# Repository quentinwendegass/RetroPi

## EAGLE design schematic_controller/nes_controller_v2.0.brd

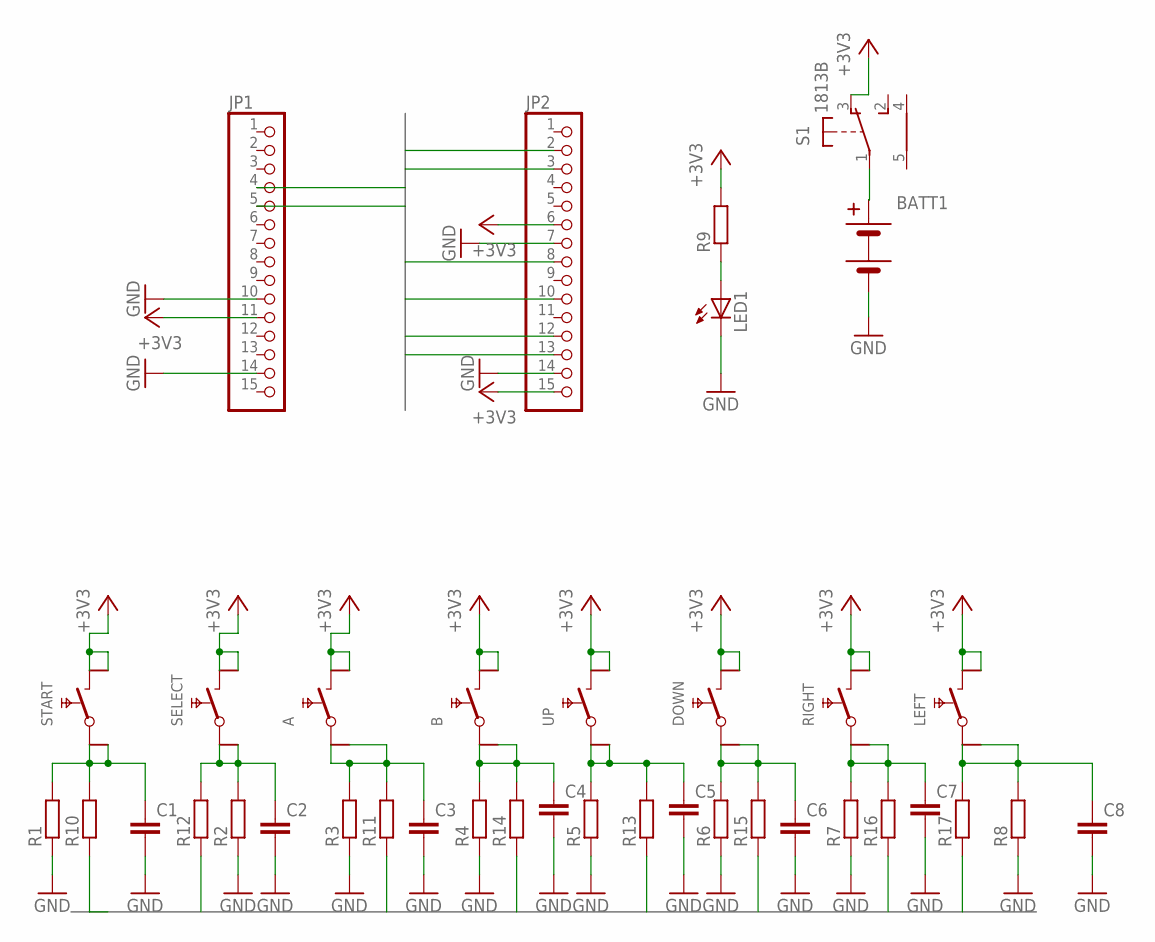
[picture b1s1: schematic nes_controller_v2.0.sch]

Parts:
A: SMDTAST
B: SMDTAST
BATT1: BATTERIEHALTER_2X_AAA; BATTERIEHALTER
C1, C2, C3, C4, C5, C6, C7, C8: C-EUC0805K; C0805K
DOWN: SMDTAST
JP1, JP2: PINHD-1X15; 1X15
LED1: LED3MM
LEFT: SMDTAST
R1, R2, R3, R4, R5, R6, R7, R8, R9, R10, R11, R12, R13, R14, R15, R16, R17: R-EU_R1206; R1206
RIGHT: SMDTAST
S1: 1813B
SELECT: SMDTAST
START: SMDTAST
UP: SMDTAST

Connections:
3§4: C2.1, R2.2, R12.2, SELECT.1, SELECT.11
4$5: A.1, A.11, C3.1, R3.2, R11.2
+3V3: A.2, A.22, B.2, B.22, DOWN.2, DOWN.22, JP1.11, JP2.6, JP2.15, LEFT.2, LEFT.22, R9.2, RIGHT.2, RIGHT.22, S1.3 (O), SELECT.2, SELECT.22, START.2, START.22, UP.2, UP.22
A: JP1.5, R11.1
B: JP1.4, R14.1
DOWN: JP2.10, R15.1
GND: BATT1.P-, C1.2, C2.2, C3.2, C4.2, C5.2, C6.2, C7.2, C8.2, JP1.10, JP1.14, JP2.7, JP2.14, LED1.K (C), R1.1, R2.1, R3.1, R4.1, R5.1, R6.1, R7.1, R8.1
LEFT: JP2.3, R17.1
unnamed: BATT1.P+, S1.1 (W)
unnamed: LED1.A, R9.1
unnamed: C1.1, R1.2, R10.2, START.1, START.11
unnamed: B.1, B.11, C4.1, R4.2, R14.2
unnamed: C5.1, R5.2, R13.2, UP.1, UP.11
unnamed: C6.1, DOWN.1, DOWN.11, R6.2, R15.2
unnamed: C7.1, R7.2, R16.2, RIGHT.1, RIGHT.11
unnamed: C8.1, LEFT.1, LEFT.11, R8.2, R17.2
RIGHT: JP2.8, R16.1
SELECT: JP2.12, R12.1
START: JP2.13, R10.1
UP: JP2.2, R13.1

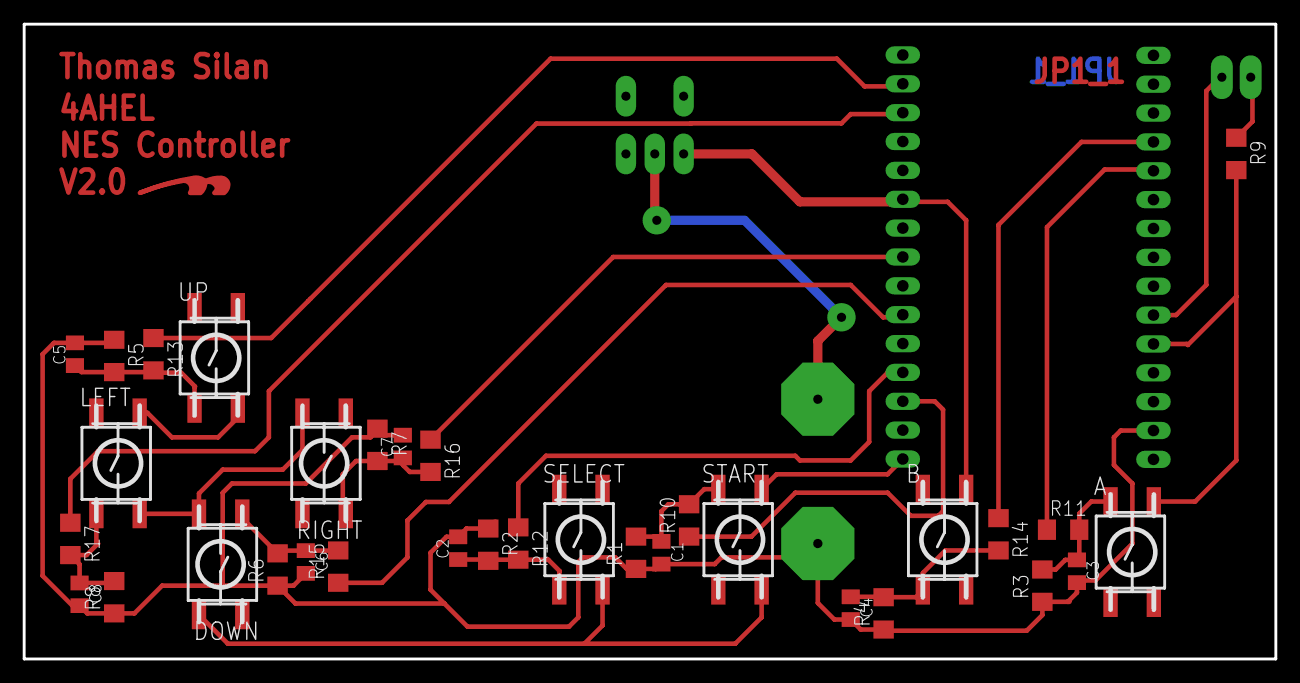
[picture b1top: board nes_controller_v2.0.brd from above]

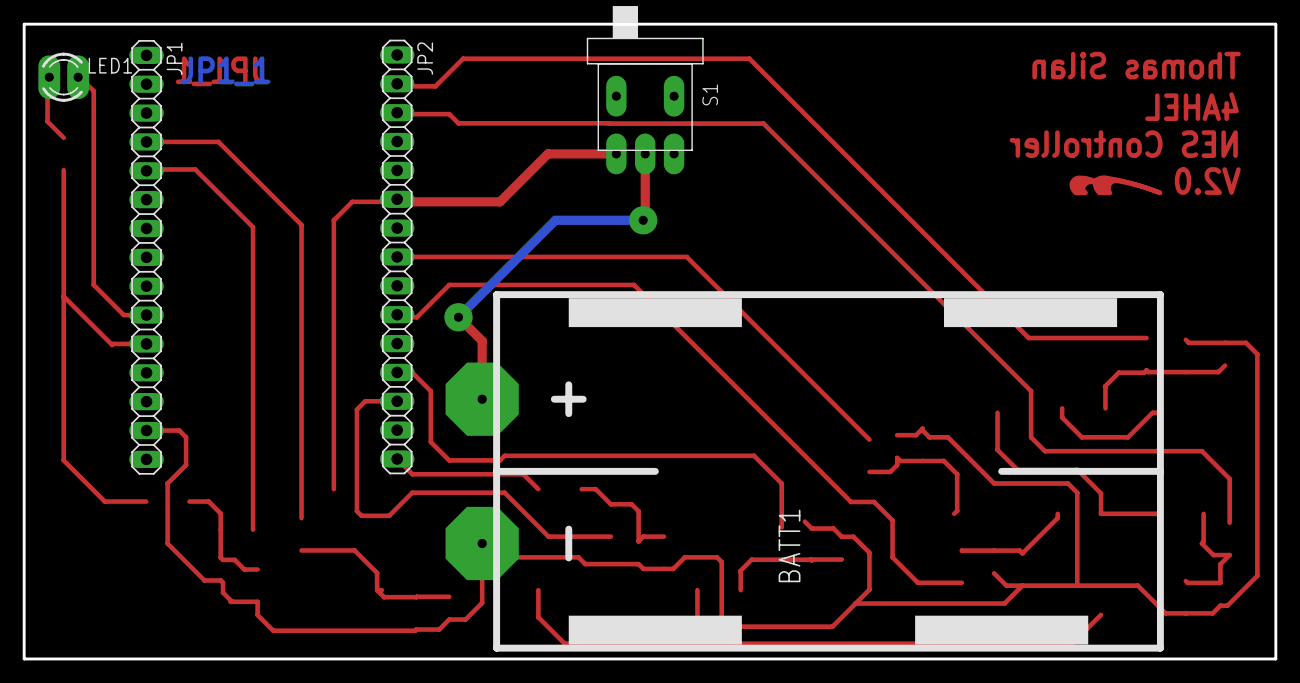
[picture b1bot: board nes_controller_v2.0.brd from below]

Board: 2 copper layers, 110.2 x 55.9 mm, 39 parts (5 on the bottom side), 20 nets.

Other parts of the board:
U$1: LOGOTOP_8

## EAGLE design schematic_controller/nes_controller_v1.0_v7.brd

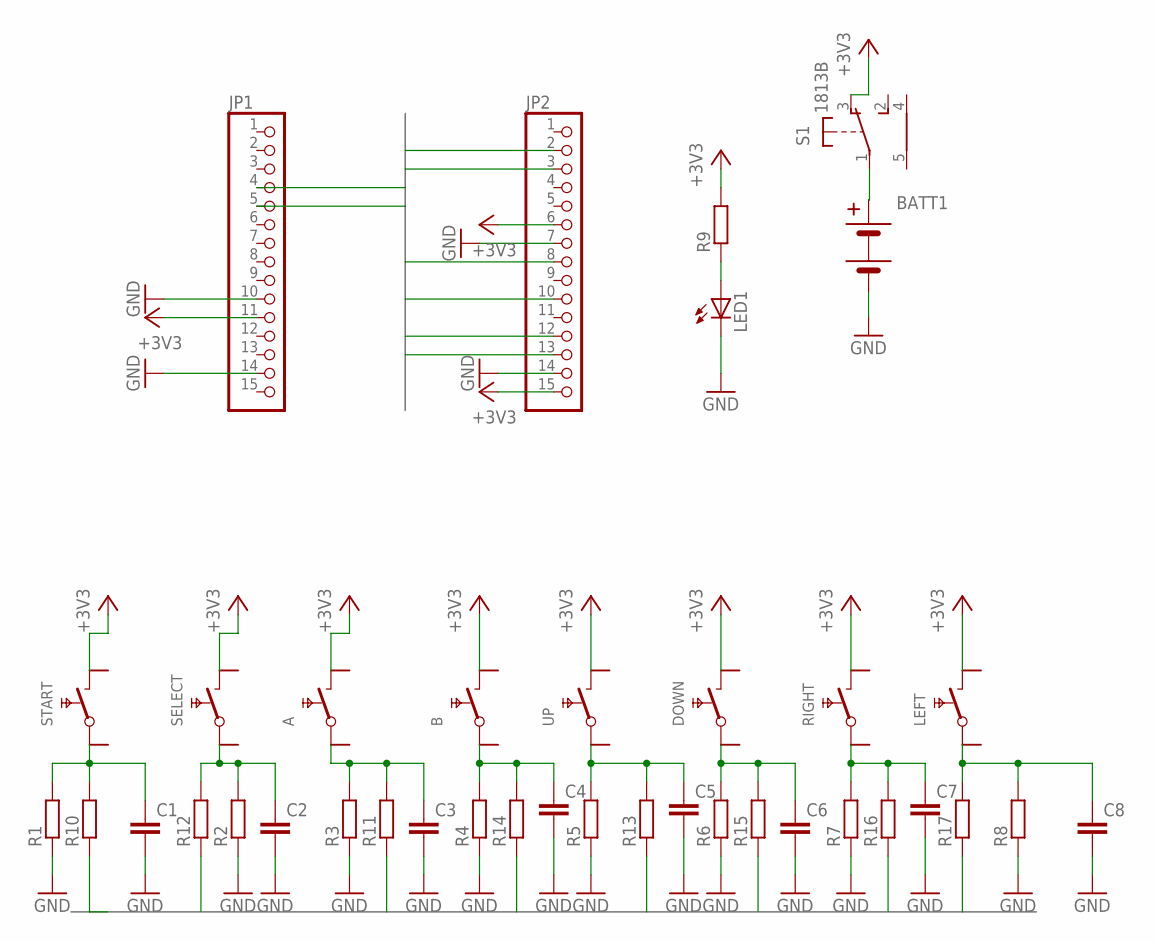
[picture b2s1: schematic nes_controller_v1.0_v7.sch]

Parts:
A: SMDTAST
B: SMDTAST
BATT1: BATTERIEHALTER_2X_AAA; BATTERIEHALTER
C1, C2, C3, C4, C5, C6, C7, C8: C-EUC0805K; C0805K
DOWN: SMDTAST
JP1, JP2: PINHD-1X15; 1X15
LED1: LED3MM
LEFT: SMDTAST
R1, R2, R3, R4, R5, R6, R7, R8, R9, R10, R11, R12, R13, R14, R15, R16, R17: R-EU_MELF0207R; MINI_MELF-0207R
RIGHT: SMDTAST
S1: 1813B
SELECT: SMDTAST
START: SMDTAST
UP: SMDTAST

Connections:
3§4: C2.1, R2.2, R12.2, SELECT.1
4$5: A.1, C3.1, R3.2, R11.2
+3V3: A.2, B.2, DOWN.2, JP1.11, JP2.6, JP2.15, LEFT.2, R9.2, RIGHT.2, S1.3 (O), SELECT.2, START.2, UP.2
A: JP1.5, R11.1
B: JP1.4, R14.1
DOWN: JP2.8, R15.1
GND: BATT1.P-, C1.2, C2.2, C3.2, C4.2, C5.2, C6.2, C7.2, C8.2, JP1.10, JP1.14, JP2.7, JP2.14, LED1.K (C), R1.1, R2.1, R3.1, R4.1, R5.1, R6.1, R7.1, R8.1
LEFT: JP2.10, R17.1
unnamed: BATT1.P+, S1.1 (W)
unnamed: LED1.A, R9.1
unnamed: C1.1, R1.2, R10.2, START.1
unnamed: B.1, C4.1, R4.2, R14.2
unnamed: C5.1, R5.2, R13.2, UP.1
unnamed: C6.1, DOWN.1, R6.2, R15.2
unnamed: C7.1, R7.2, R16.2, RIGHT.1
unnamed: C8.1, LEFT.1, R8.2, R17.2
RIGHT: JP2.13, R16.1
SELECT: JP2.2, R12.1
START: JP2.3, R10.1
UP: JP2.12, R13.1

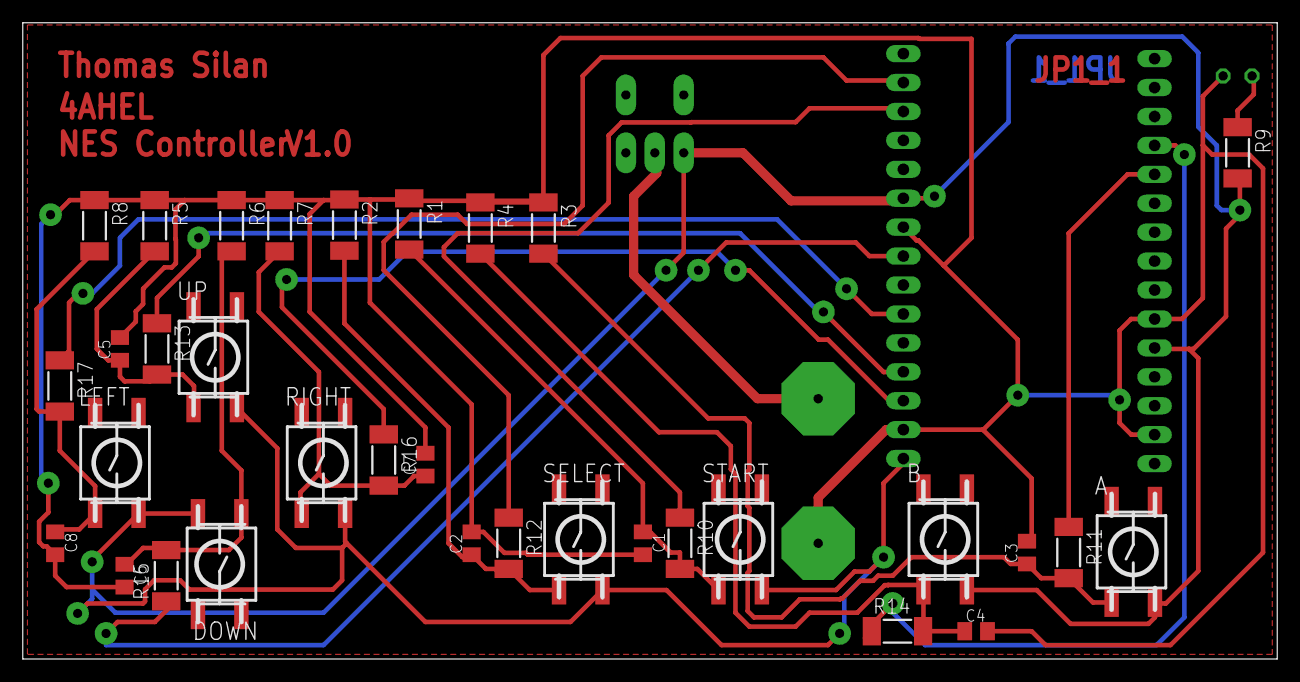
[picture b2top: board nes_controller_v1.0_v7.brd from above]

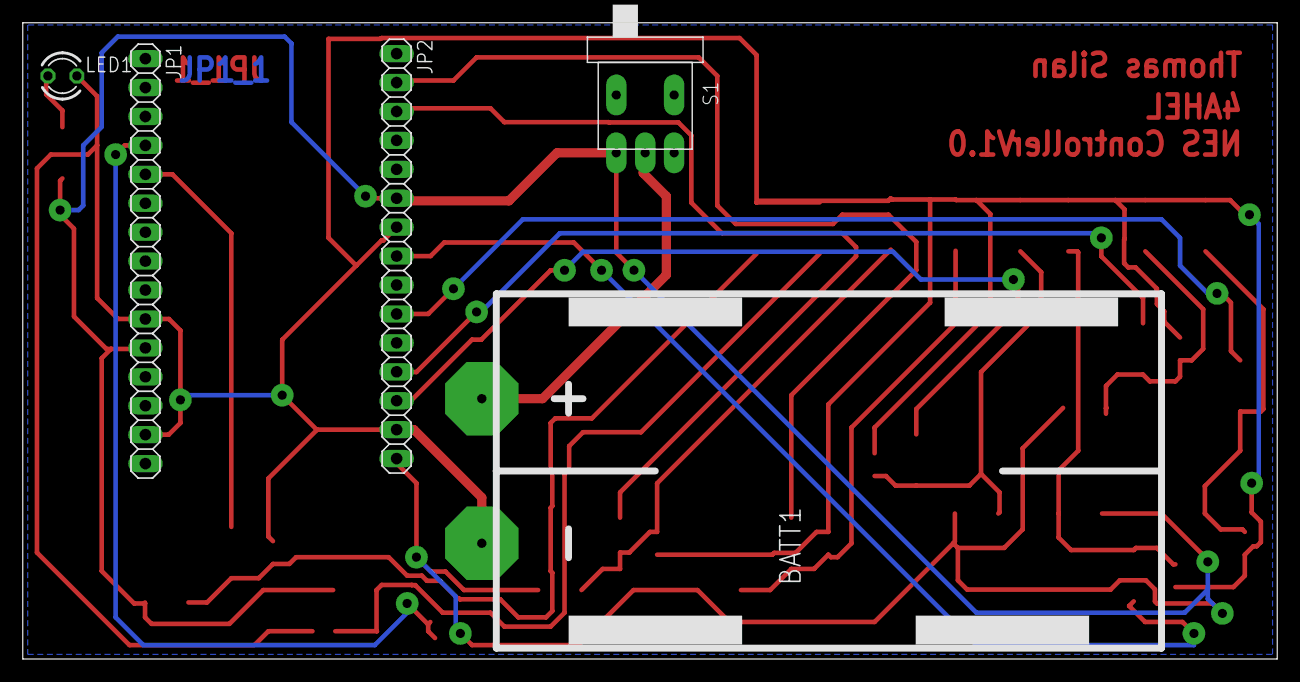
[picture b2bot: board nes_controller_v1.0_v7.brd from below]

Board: 2 copper layers, 110.2 x 55.9 mm, 38 parts (5 on the bottom side), 20 nets.

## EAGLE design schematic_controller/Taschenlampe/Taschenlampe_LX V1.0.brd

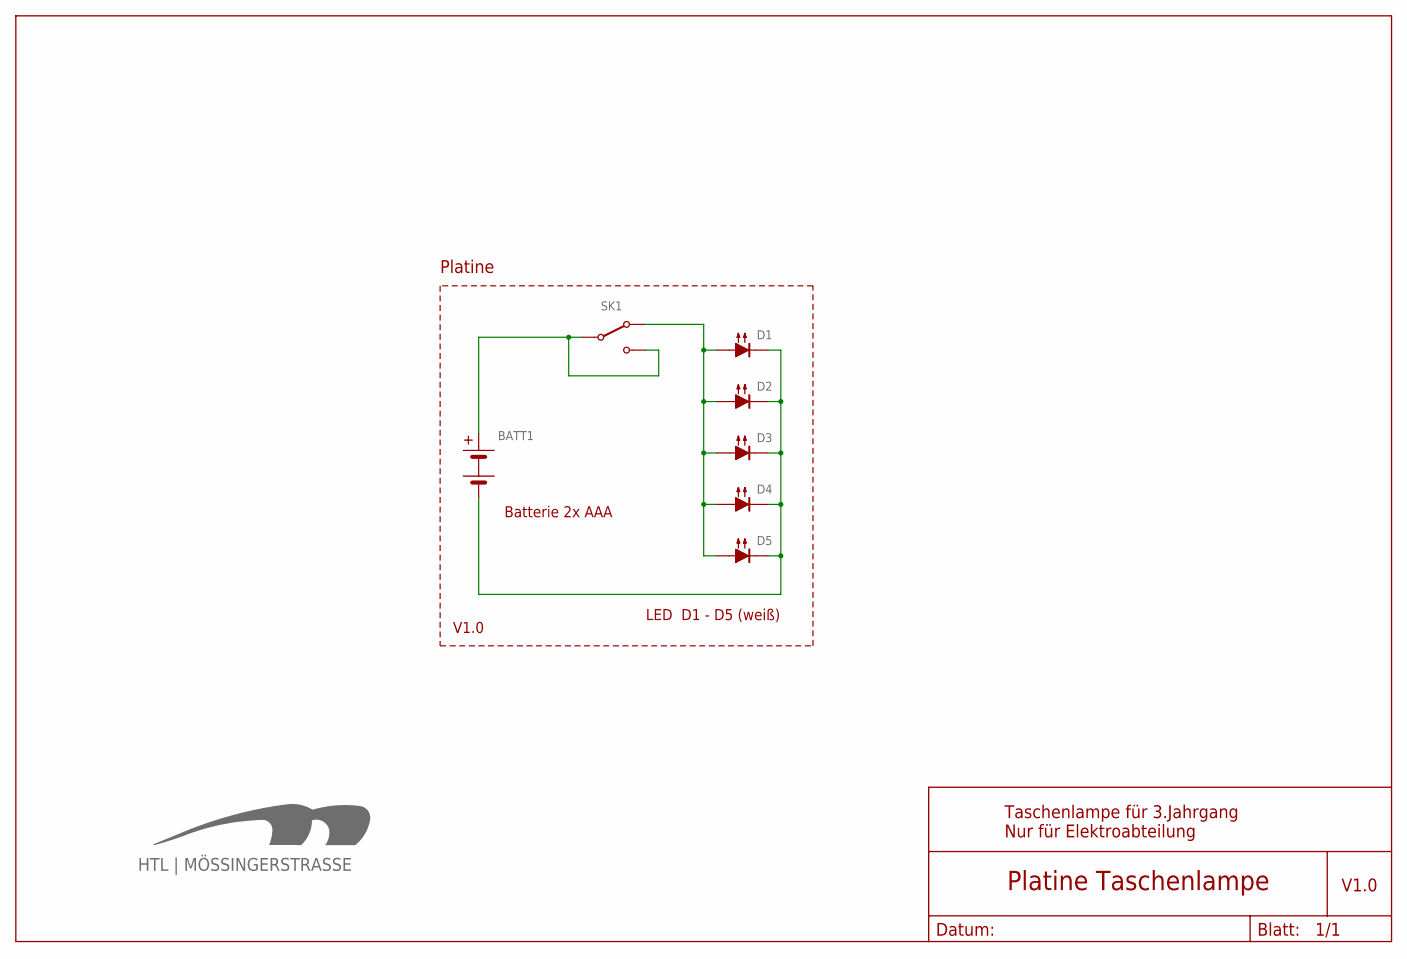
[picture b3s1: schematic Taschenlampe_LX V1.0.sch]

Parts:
BATT1: BATTERIEHALTER_2X_AAA; BATTERIEHALTER
D1, D2, D3, D4, D5: LEUCHTDIODE_DIN_ALT; LEUCHTDIODE
SK1: SCHALTER
U$2: HTL_LOGOBOT_15MM; LOGOBOT_15

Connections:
unnamed: BATT1.P+, SK1.P, SK1.P2
unnamed: D1.A, D2.A, D3.A, D4.A, D5.A, SK1.P1
unnamed: BATT1.P-, D1.K, D2.K, D3.K, D4.K, D5.K

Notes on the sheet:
Platine
Batterie 2x AAA
Taschenlampe für 3.Jahrgang Nur für Elektroabteilung
Platine Taschenlampe
V1.0
LED D1 - D5 (weiß)

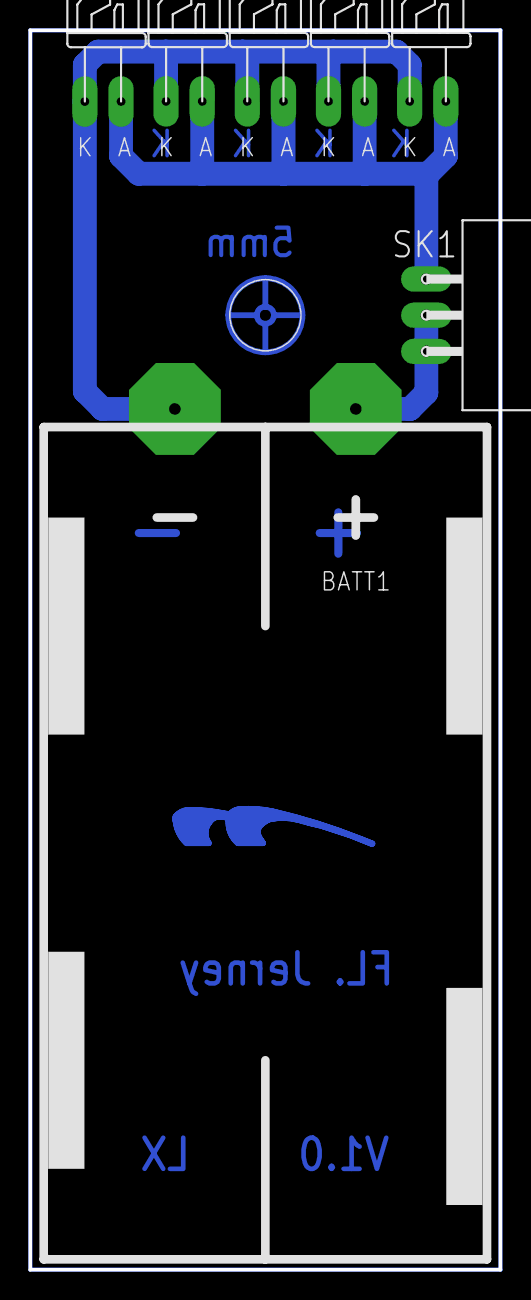
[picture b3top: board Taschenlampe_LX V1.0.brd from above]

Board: 2 copper layers, 33.0 x 87.0 mm, 9 parts (0 on the bottom side), 3 nets.

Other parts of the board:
LOGO: LOGOBOT_15

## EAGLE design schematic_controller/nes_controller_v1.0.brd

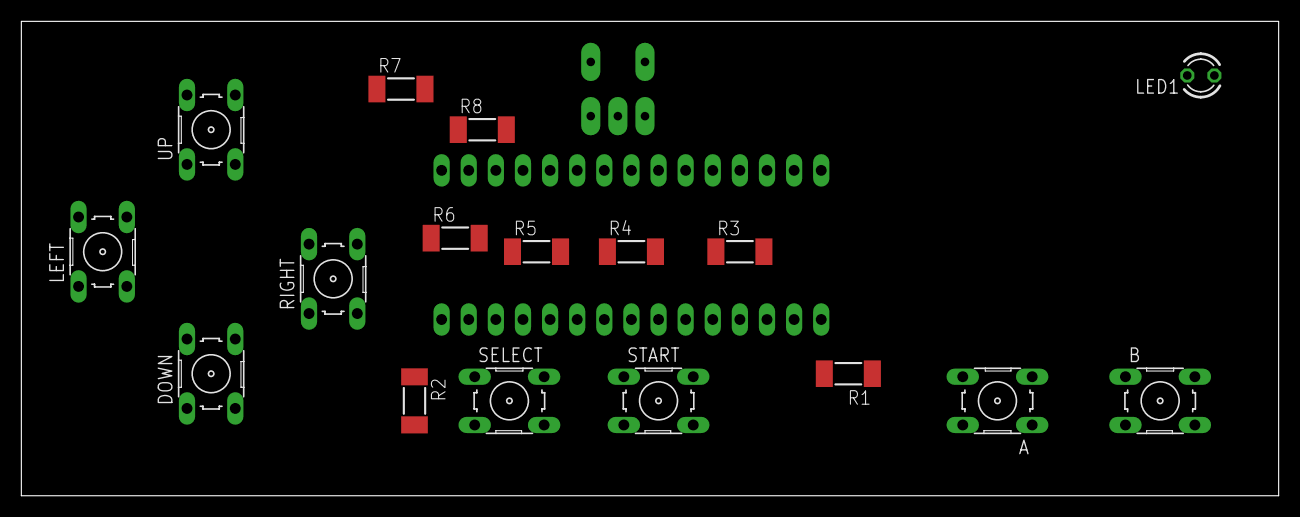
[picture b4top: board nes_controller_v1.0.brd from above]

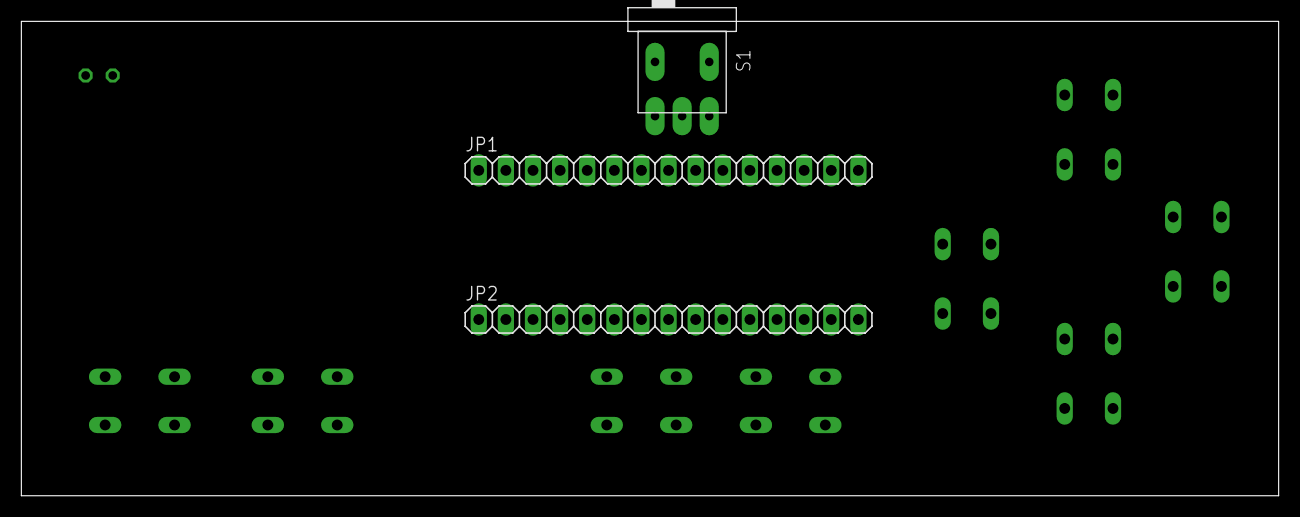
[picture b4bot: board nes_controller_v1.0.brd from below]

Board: 2 copper layers, 117.8 x 44.4 mm, 20 parts (3 on the bottom side), 11 nets, no tracks yet.

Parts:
A: B3F-10XX
B: B3F-10XX
DOWN: B3F-10XX
JP1, JP2: 1X15
LED1: LED3MM
LEFT: B3F-10XX
R1, R2, R3, R4, R5, R6, R7, R8: MINI_MELF-0207R
RIGHT: B3F-10XX
S1: 1813B
SELECT: B3F-10XX
START: B3F-10XX
UP: B3F-10XX

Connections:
+3V3: A.1, A.2, B.1, B.2, DOWN.1, DOWN.2, JP1.11, JP2.6, JP2.15, LEFT.1, LEFT.2, RIGHT.1, RIGHT.2, S1.2, SELECT.1, SELECT.2, START.1, START.2, UP.1, UP.2
A: A.3, A.4, JP2.3, R3.2
B: B.3, B.4, JP2.4, R4.2
DOWN: DOWN.3, DOWN.4, JP2.11, R6.2
GND: JP1.10, JP1.14, JP2.7, JP2.14, LED1.K, R1.1, R2.1, R3.1, R4.1, R5.1, R6.1, R7.1, R8.1
LEFT: JP2.10, LEFT.3, LEFT.4, R8.2
unnamed: LED1.A, S1.1
RIGHT: JP2.9, R7.2, RIGHT.3, RIGHT.4
SELECT: JP2.1, R2.2, SELECT.3, SELECT.4
START: JP2.2, R1.2, START.3, START.4
UP: JP2.12, R5.2, UP.3, UP.4

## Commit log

2017-11-24 Push to Github
2017-11-24 Set .gitignore
2017-11-24 Added simple LED Test
2017-12-06 Added uinput module
2017-12-06 Bug fixes
2017-12-06 controller website added
2017-12-06 Fixes and cleanup
2017-12-07 Added web app manifest
2017-12-08 bug fixes and updated webpage
2017-12-08 changed system for multiple clients
2017-12-13 added 3D models
2017-12-13 added nes_controller_v1.0.sch without batteryholder as power supply
2017-12-14 changed 3d models
2017-12-14 changed schematic
2017-12-15 changed 3d controller cross bittons
2017-12-15 added bord layer
2017-12-15 added board layer and 3d ontroller
2017-12-16 Added Software for Client on NodeMCU
2017-12-17 Updated Pinout
2017-12-18 new command line interface
2017-12-18 setup led indicator
2017-12-19 fixed bugs in command line helper
2017-12-19 Removed unnecessary files and websocket library
2017-12-19 Updated controller software and changed pinout
2017-12-20 Added script for start rom and renamed server.py
2017-12-20 fixed bug
2018-01-11 added copntroller v 2
2018-01-11 finishd 3d model of controller verson 2
2018-01-11 updated pin layout
2018-01-11 updated schematic and board layout to new pin layout
2018-01-11 updated moard layout
2018-01-11 finished controller v2
2018-01-11 finished board layout
2018-01-13 updated schematic with debounced buttons
2018-01-17 added .stl files for 3d printing
2018-01-18 changed bigger led hole
2018-01-18 added PCB replacement
2018-01-19 Added Icon for Android
2018-02-03 added Documentation
2018-02-03 added schematic and board for eaglev7
2018-02-03 changed schematic and boart to v2
2018-02-06 added branche 'thomas' for testing
2018-02-06 testet
2018-02-06 changed onstart.sh
2018-02-07 changed board layout
2018-02-07 changed board layout eaglev7
2018-02-07 xhanged board layout and board layout eralge v7
2018-03-07 changed Controller measurements to fix button space problems
2018-03-08 Changed Controller dimensions dor the buttons
2018-03-17 added eagle libaries
    added eagle libaries
